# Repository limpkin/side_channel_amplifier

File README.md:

# side_channel_amplifier
Repository containing the side channel amplifier boards presented at hardwear.io

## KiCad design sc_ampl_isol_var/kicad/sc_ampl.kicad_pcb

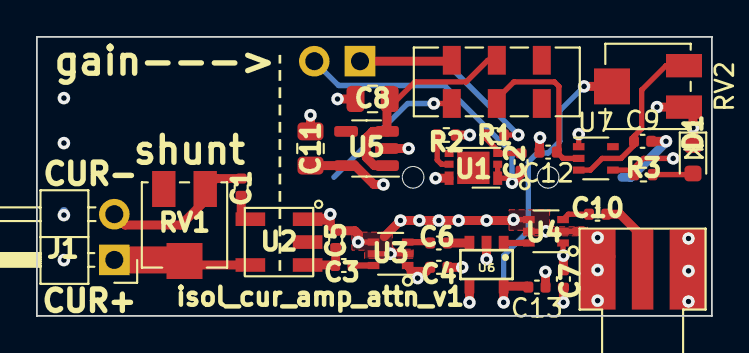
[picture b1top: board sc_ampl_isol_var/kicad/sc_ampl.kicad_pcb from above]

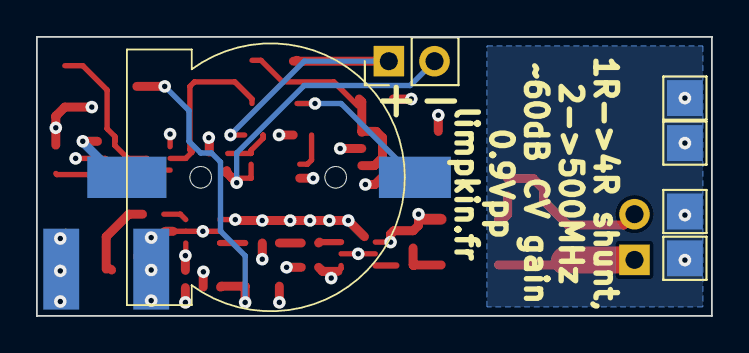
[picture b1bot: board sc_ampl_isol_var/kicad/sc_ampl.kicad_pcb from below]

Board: 4 copper layers, 37.5 x 15.5 mm, 35 parts (6 on the bottom side), 23 nets.

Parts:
BT1: Battery_Cell; PinHeader_1x02_P2.54mm_Vertical
BT2: Battery_Cell; CR1220_THZ_HOLDER
C1: 10nF; C_0402_1005Metric
C2: 100n; C_0402_1005Metric
C3, C4, C6, C7, C10, C13: 1nF; C_0402_1005Metric
C5: 4.7pF; C_0402_1005Metric
C8, C11: 22uF; C_0805_2012Metric
C9, C12: 2.2uF; C_0402_1005Metric
D1: LED; LED_0603_1608Metric
J1: Conn_01x02_Pin; PinHeader_1x02_P2.54mm_Horizontal
J2: COAX; SMA_ALIEXPRESS
R1: 453; R_0402_1005Metric
R2, R3: 1k; R_0402_1005Metric
RV1: 10; Potentiometer_Bourns_3314J_Vertical
RV2: 100k; Potentiometer_Bourns_3314J_Vertical
SW1: SW_DPDT_x2; SW_DPDT_CK_JS202011JCQN
TP2, TP3, TP5, TP6: TestPoint; TestPoint_Pad_2.0x2.0mm
U1: UDFN-6-1EP_3x2mm_P0.6mm_EP1.7x1.7mm
U2: TC8-1+; TC2-72T+
U3: BGA2803; SOT-363_SC-70-6
U4: BGA2802; SOT-363_SC-70-6
U5: NCP163ASN330T1G; SOT-23-5
U6: MAAVSS0006TR-3000; SOT25
U7: RP117Q252D; SOT-353_SC-70-5

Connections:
+3V3: C4.1, C7.1, C11.1, R3.1, U3.1 (Vcc), U4.1 (Vcc), U5.5 (OUT), U7.4 (CE)
/RTN: TP2.1, TP3.1, TP5.1, TP6.1
GND: BT2.1 (+), C4.2, C5.2, C7.2, C8.2, C9.2, C11.2, C12.2, C13.1, D1.1 (K), J2.2 (Ext), R2.1, RV2.1, U1.6 (S2), U2.1, U3.2 (G), U3.4 (G), U3.5 (G), U4.2 (G), U4.4 (G), U4.5 (G), U5.2 (GND), U6.2 (GND), U6.4 (GND), U7.1 (GND)
unnamed: BT1.1 (+), R1.2, SW1.1 (A)
unnamed: BT1.2 (-), C2.2, U1.1 (S1), U1.2 (VSS)
unnamed: BT2.2 (-), SW1.4 (A)
unnamed: C1.2, U2.6
unnamed: C3.1, C5.1, U2.3
unnamed: C3.2, U3.6
unnamed: C6.1, U3.3
unnamed: C6.2, U6.3 (RF)
unnamed: C10.1, U4.3
unnamed: D1.2 (A), R3.2
unnamed: J1.1, RV1.2, U2.4
unnamed: C1.1, J1.2, RV1.1
unnamed: C10.2, J2.1 (In)
unnamed: C8.1, SW1.2 (B), U5.1 (IN), U5.3 (EN)
unnamed: C12.1, SW1.5 (B), U7.2 (VDD)
unnamed: C2.1, R1.1, U1.3 (VDD)
unnamed: R2.2, U1.5 (VM)
unnamed: U4.6, U6.1 (RF)
unnamed: C13.2, RV2.2, U6.5 (VC)
unnamed: C9.1, RV2.3, U7.3 (VOUT)

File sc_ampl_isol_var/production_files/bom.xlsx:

Item | Qty | Reference(s) | Value | Manufacturer | Manufacturer Part Number | URL
1 | 1 | BT1 | 18650 holder with wires |  |  | https://www.aliexpress.com/item/1005005084346241.html
2 | 1 | BT2 | CR1220 holder |  |  | https://www.aliexpress.com/item/1005005296534801.html
3 | 1 | C1 | 10nF | Murata Electronics | GCM155R71H103KA55D | https://www.digikey.com/en/products/detail/murata-electronic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
4 | 1 | C2 | 100n | KYOCERA AVX | KGM05AR71C104KH | https://www.digikey.com/en/products/detail/kyocera-avx/0402Y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
5 | 6 | C3, C4, C6, C7, C10, C13 | 1nF | Murata Electronics | GCM155R71H102KA37D | https://www.digikey.com/en/products/detail/murata-electronic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
6 | 1 | C5 | 4.7pF | Murata Electronics | GRM1555C1H4R7CA01D | https://www.digikey.com/en/products/detail/murata-electronic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
7 | 2 | C8, C11 | 22uF | Samsung Electro-Mechanics | CL21A226MOCLRNC | https://www.digikey.com/product-detail/en/samsung-electro-me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
8 | 2 | C9, C12 | 2.2uF | Murata Electronics | GRM155R61E225ME11D | https://www.digikey.com/en/products/detail/murata-electronic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
9 | 1 | D1 | LED | Lumex Opto/Components Inc. | SML-LX0603GW-TR | https://www.digikey.com/en/products/detail/lumex-opto-compon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
10 | 1 | J1 | Conn_01x02_Pin | Amphenol ICC (FCI) | 10129379-902002BLF | https://www.digikey.com/en/products/detail/amphenol-cs-fci/1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
11 | 1 | J2 | COAX | 1.6mm edge SMA connector |  | https://www.aliexpress.com/item/1005001943804637.html
12 | 1 | R1 | 453 | YAGEO | RC0402FR-07453RL | https://www.digikey.com/en/products/detail/yageo/RC0402FR-07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
13 | 2 | R2, R3 | 1k | Stackpole Electronics Inc | RMCF0402FT1K00 | https://www.digikey.com/en/products/detail/stackpole-electro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
14 | 1 | RV1 | 10 | Bourns Inc. | 3314J-1-100E | https://www.digikey.com/en/products/detail/bourns-inc/3314J-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
15 | 1 | RV2 | 100k | Bourns Inc. | 3314J-1-104E | https://www.digikey.com/en/products/detail/bourns-inc/3314J-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
16 | 1 | SW1 | SW_DPDT_x2 | C&K | JS202011JCQN | https://www.digikey.com/en/products/detail/c-k/JS202011JCQN/6137630
18 | 1 | U1 | ~ | Diodes Incorporated | AP9211SA-AH-HAC-7 | https://www.digikey.com/en/products/detail/diodes-incorporat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
19 | 1 | U2 | TC8-1+ | Mini-Circuits | TC8-1+ | https://www.digikey.com/en/products/detail/mini-circuits/TC8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
20 | 1 | U3 | BGA2803 | NXP USA Inc. | BGA2803,115 | https://www.digikey.com/en/products/detail/nxp-usa-inc/BGA28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
21 | 1 | U4 | BGA2802 | NXP USA Inc. | IC RF AMP GPS 0HZ-2.2GHZ 6TSSOP | https://www.digikey.com/en/products/detail/nxp-usa-inc/BGA28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
22 | 1 | U5 | NCP163ASN330T1G | onsemi | NCP163ASN330T1G | https://www.digikey.com/product-detail/en/on-semiconductor/N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
23 | 1 | U6 | MAAVSS0006TR-3000 | MACOM Technology Solutions | MAAVSS0006TR-3000 | https://www.digikey.com/en/products/detail/macom-technology-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
24 | 1 | U7 | RP117Q252D | Nisshinbo Micro Devices Inc. | RP117Q252D-TR-FE | https://www.digikey.com/en/products/detail/nisshinbo-micro-d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

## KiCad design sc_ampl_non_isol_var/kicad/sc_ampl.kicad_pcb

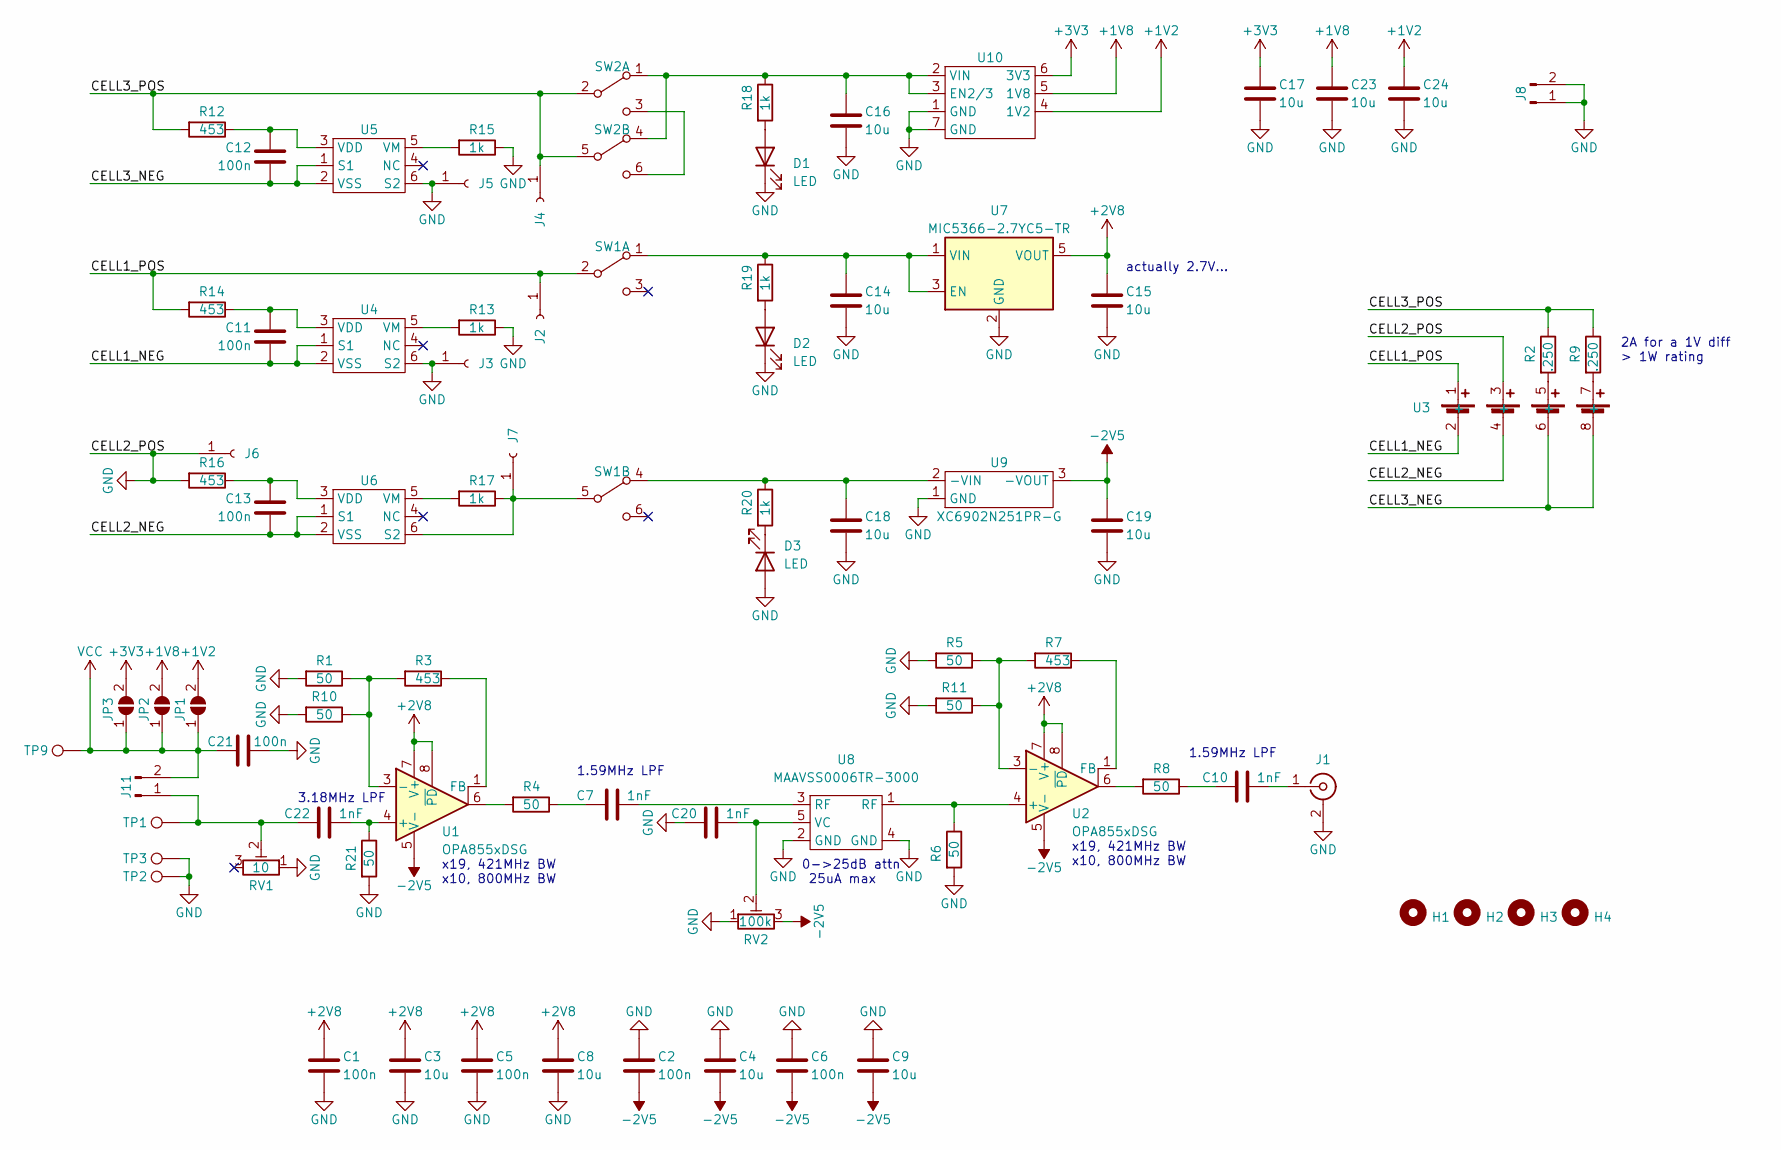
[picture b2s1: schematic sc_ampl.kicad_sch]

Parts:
C1, C2, C5, C6, C11, C12, C13, C21: 100n; C_0402_1005Metric
C3, C4, C8, C9, C14, C15, C16, C17, C18, C19, C23, C24: 10u; C_0603_1608Metric
C7, C10, C20, C22: 1nF; C_0402_1005Metric
D1, D2, D3: LED; LED_0603_1608Metric
H1, H2, H3, H4: MountingHole; MountingHole_2.5mm
J1: COAX; SMA_ALIEXPRESS
J2, J3, J4, J5, J6, J7: Conn_01x01_Socket; 575-8
J8, J11: Conn_01x02_Pin; PinHeader_1x02_P2.54mm_Horizontal
JP1, JP2, JP3: SolderJumper_2_Open; SolderJumper-2_P1.3mm_Open_TrianglePad1.0x1.5mm
R1, R4, R5, R6, R8, R10, R11, R21: 50; R_0402_1005Metric
R2, R9: .250; R_2512_6332Metric
R3, R7, R12, R14, R16: 453; R_0402_1005Metric
R13, R15, R17, R18, R19, R20: 1k; R_0402_1005Metric
RV1: 10; Potentiometer_Bourns_3314J_Vertical
RV2: 100k; Potentiometer_Bourns_3314J_Vertical
SW1, SW2: SW_DPDT_x2; SW_DPDT_CK_JS202011JCQN
TP1, TP2, TP3, TP9: TestPoint; TestPoint_Pad_2.0x2.0mm
U1, U2: OPA855xDSG; WSON-8-1EP_2x2mm_P0.5mm_EP0.9x1.6mm
U3: 4x_18650_smd
U4, U5, U6: UDFN-6-1EP_3x2mm_P0.6mm_EP1.7x1.7mm
U7: MIC5366-2.7YC5-TR; SOT-353_SC-70-5
U8: MAAVSS0006TR-3000; SOT25
U9: XC6902N251PR-G; SOT-89-3
U10: MLF-6-1EP_1.6x1.6mm_P0.5mm_EP0.5x1.26mm

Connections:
+1V2: C24.1, JP1.2 (B), U10.4 (1V2)
+1V8: C23.1, JP2.2 (B), U10.5 (1V8)
+2V8: C1.1, C3.1, C5.1, C8.1, C15.1, U1.7 (V+), U1.8 (~PD), U2.7 (V+), U2.8 (~PD), U7.5 (VOUT)
+3V3: C17.1, JP3.2 (B), U10.6 (3V3)
-2V5: C2.2, C4.2, C6.2, C9.2, C19.1, RV2.3, U1.5 (V-), U1.9 (V-), U2.5 (V-), U2.9 (V-), U9.3 (-VOUT)
/CELL1_NEG: C11.2, U3.2 (-), U4.1 (S1), U4.2 (VSS)
/CELL1_POS: J2.1, R14.2, SW1.2 (B), U3.1 (+)
/CELL2_NEG: C13.2, U3.4 (-), U6.1 (S1), U6.2 (VSS)
/CELL3_NEG: C12.2, U3.6 (-), U3.8 (-), U5.1 (S1), U5.2 (VSS)
/CELL3_POS: J4.1, R2.1, R9.1, R12.2, SW2.2 (B), SW2.5 (B)
GND: C1.2, C2.1, C3.2, C4.1, C5.2, C6.1, C8.2, C9.1, C14.2, C15.2, C16.2, C17.2, C18.2, C19.2, C20.1, C21.2, C23.2, C24.2, D1.1 (K), D2.1 (K), D3.2 (A), J1.2 (Ext), J3.1, J5.1, J6.1, J8.1, J8.2, R1.2, R5.2, R6.2, R10.2, R11.2, R13.1, R15.1, R16.2, R21.2, RV1.1, RV2.1, TP2.1, TP3.1, U3.3 (+), U4.6 (S2), U5.6 (S2), U7.2 (GND), U8.2 (GND), U8.4 (GND), U9.1 (GND), U10.1 (GND), U10.7 (GND)
unnamed: C7.1, R4.1
unnamed: C7.2, U8.3 (RF)
unnamed: C10.1, R8.1
unnamed: D1.2 (A), R18.2
unnamed: D2.2 (A), R19.2
unnamed: D3.1 (K), R20.2
unnamed: C10.2, J1.1 (In)
unnamed: J7.1, R17.1, SW1.5 (B), U6.6 (S2)
unnamed: C22.1, J11.1, RV1.2, TP1.1
unnamed: R2.2, U3.5 (+)
unnamed: R4.2, U1.6
unnamed: R8.2, U2.6
unnamed: R9.2, U3.7 (+)
unnamed: C14.1, R19.1, SW1.1 (A), U7.1 (VIN), U7.3 (EN)
unnamed: C18.1, R20.1, SW1.4 (A), U9.2 (-VIN)
unnamed: C16.1, R18.1, SW2.1 (A), SW2.4 (A), U10.2 (VIN), U10.3 (EN2/3)
unnamed: SW2.3 (C), SW2.6 (C)
unnamed: C22.2, R21.1, U1.4 (+)
unnamed: R1.1, R3.2, R10.1, U1.3 (-)
unnamed: R3.1, U1.1 (FB)
unnamed: R6.1, U2.4 (+), U8.1 (RF)
unnamed: R5.1, R7.2, R11.1, U2.3 (-)
unnamed: R7.1, U2.1 (FB)
unnamed: C11.1, R14.1, U4.3 (VDD)
unnamed: R13.2, U4.5 (VM)
unnamed: C12.1, R12.1, U5.3 (VDD)
unnamed: R15.2, U5.5 (VM)
unnamed: C13.1, R16.1, U6.3 (VDD)
unnamed: R17.2, U6.5 (VM)
unnamed: C20.2, RV2.2, U8.5 (VC)
VCC: C21.1, J11.2, JP1.1 (A), JP2.1 (A), JP3.1 (A), TP9.1

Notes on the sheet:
x19, 421MHz BW x10, 800MHz BW
actually 2.7V...
0->25dB attn 25uA max
1.59MHz LPF
3.18MHz LPF
2A for a 1V diff > 1W rating

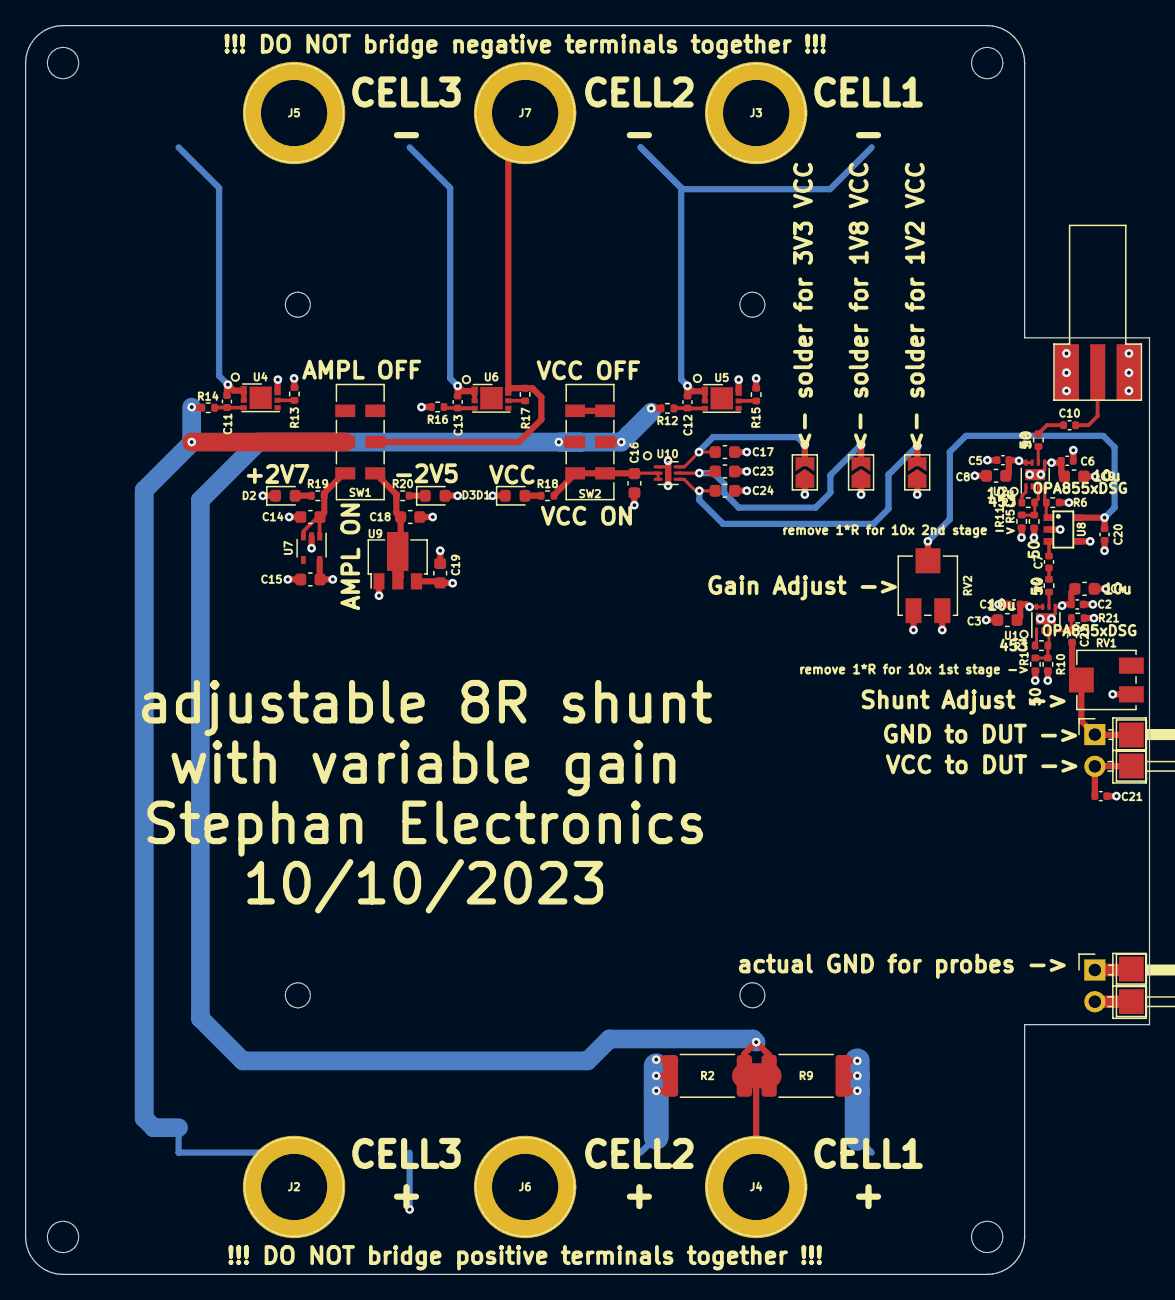
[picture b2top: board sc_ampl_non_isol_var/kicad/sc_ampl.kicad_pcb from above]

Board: 4 copper layers, 90.0 x 100.0 mm, 82 parts (1 on the bottom side), 42 nets.

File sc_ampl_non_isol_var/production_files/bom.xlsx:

Item | Qty | Reference(s) | Value | Manufacturer | Manufacturer Part Number | URL
1 | 8 | C1, C2, C5, C6, C11, C12, C13, C21 | 100n | KYOCERA AVX | KGM05AR71C104KH | https://www.digikey.com/en/products/detail/kyocera-avx/0402Y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
2 | 12 | C3, C4, C8, C9, C14, C15, C16, C17, C18, C19, C23, C24 | 10u | Samsung Electro-Mechanics | CL10A106MQ8NNNC | https://www.digikey.com/en/products/detail/samsung-electro-m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
3 | 4 | C7, C10, C20, C22 | 1nF | Murata Electronics | GCM155R71H102KA37D | https://www.digikey.ch/en/products/detail/murata-electronics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
4 | 3 | D1, D2, D3 | LED | Lumex Opto/Components Inc. | SML-LX0603GW-TR | https://www.digikey.com/en/products/detail/lumex-opto-compon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
6 | 1 | J1 | COAX |  | SMA edge connector | https://www.aliexpress.com/item/1005001943804637.html
7 | 6 | J2, J3, J4, J5, J6, J7 | Conn_01x01_Socket | Keystone Electronics | 575-8 | https://www.digikey.com/en/products/detail/keystone-electron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
8 | 2 | J8, J11 | Conn_01x02_Pin | Amphenol ICC (FCI) | 10129379-902002BLF | https://www.digikey.com/en/products/detail/amphenol-cs-fci/1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
10 | 8 | R1, R4, R5, R6, R8, R10, R11, R21 | 50 | Panasonic Electronic Components | ERJ-2RKF49R9X | https://www.digikey.com/en/products/detail/panasonic-electro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
11 | 2 | R2, R9 | 0.25 | Stackpole Electronics Inc | RMCF2512FT249R | https://www.digikey.com/en/products/detail/stackpole-electro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
12 | 5 | R3, R7, R12, R14, R16 | 453 | YAGEO | RC0402FR-07453RL | https://www.digikey.com/en/products/detail/yageo/RC0402FR-07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
13 | 6 | R13, R15, R17, R18, R19, R20 | 1k | Stackpole Electronics Inc | RMCF0402FT1K00 | https://www.digikey.com/en/products/detail/stackpole-electro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
14 | 1 | RV1 | 10 | Bourns Inc. | 3314J-1-100E | https://www.digikey.com/en/products/detail/bourns-inc/3314J-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
15 | 1 | RV2 | 100k | Bourns Inc. | 3314J-1-104E | https://www.digikey.com/en/products/detail/bourns-inc/3314J-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
16 | 2 | SW1, SW2 | SW_DPDT_x2 | C&K | JS202011JCQN | https://www.digikey.com/en/products/detail/c-k/JS202011JCQN/6137630
17 | 2 | U1, U2 | OPA855xDSG | Texas Instruments | OPA855IDSGT | https://www.digikey.com/en/products/detail/texas-instruments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
19 | 1 | U3 | ~ |  | 4x 18650 holder | https://www.aliexpress.com/item/1005004221055140.html
20 | 3 | U4, U5, U6 | ~ | Diodes Incorporated | AP9211SA-AH-HAC-7 | https://www.digikey.com/en/products/detail/diodes-incorporat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
21 | 1 | U7 | MIC5366-2.7YC5-TR | Microchip Technology | MIC5366-2.7YC5-TR | https://www.digikey.com/en/products/detail/microchip-technol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
22 | 1 | U8 | MAAVSS0006TR-3000 | MACOM Technology Solutions | MAAVSS0006TR-3000 | https://www.digikey.com/en/products/detail/macom-technology-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
23 | 1 | U9 | XC6902N251PR-G | Torex Semiconductor Ltd | XC6902N251PR-G | https://www.digikey.com/en/products/detail/torex-semiconduct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
24 | 1 | U10 | ~ | Microchip Technology | MIC5387-SG4YMT-TR | https://www.digikey.com/en/products/detail/microchip-technol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

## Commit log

2023-10-28 adding fixed gain isolated amplifier
2023-11-14 adding 2 other platforms
2023-11-14 adding kicad lib
